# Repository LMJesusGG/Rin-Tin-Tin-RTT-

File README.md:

# Rin-Tin-Tin-RTT
Battlebot controlado a distancia, por medio de un microprocesador ESP 32 Wroom, tipo Drum Spinner inspirado en el Minotaur.

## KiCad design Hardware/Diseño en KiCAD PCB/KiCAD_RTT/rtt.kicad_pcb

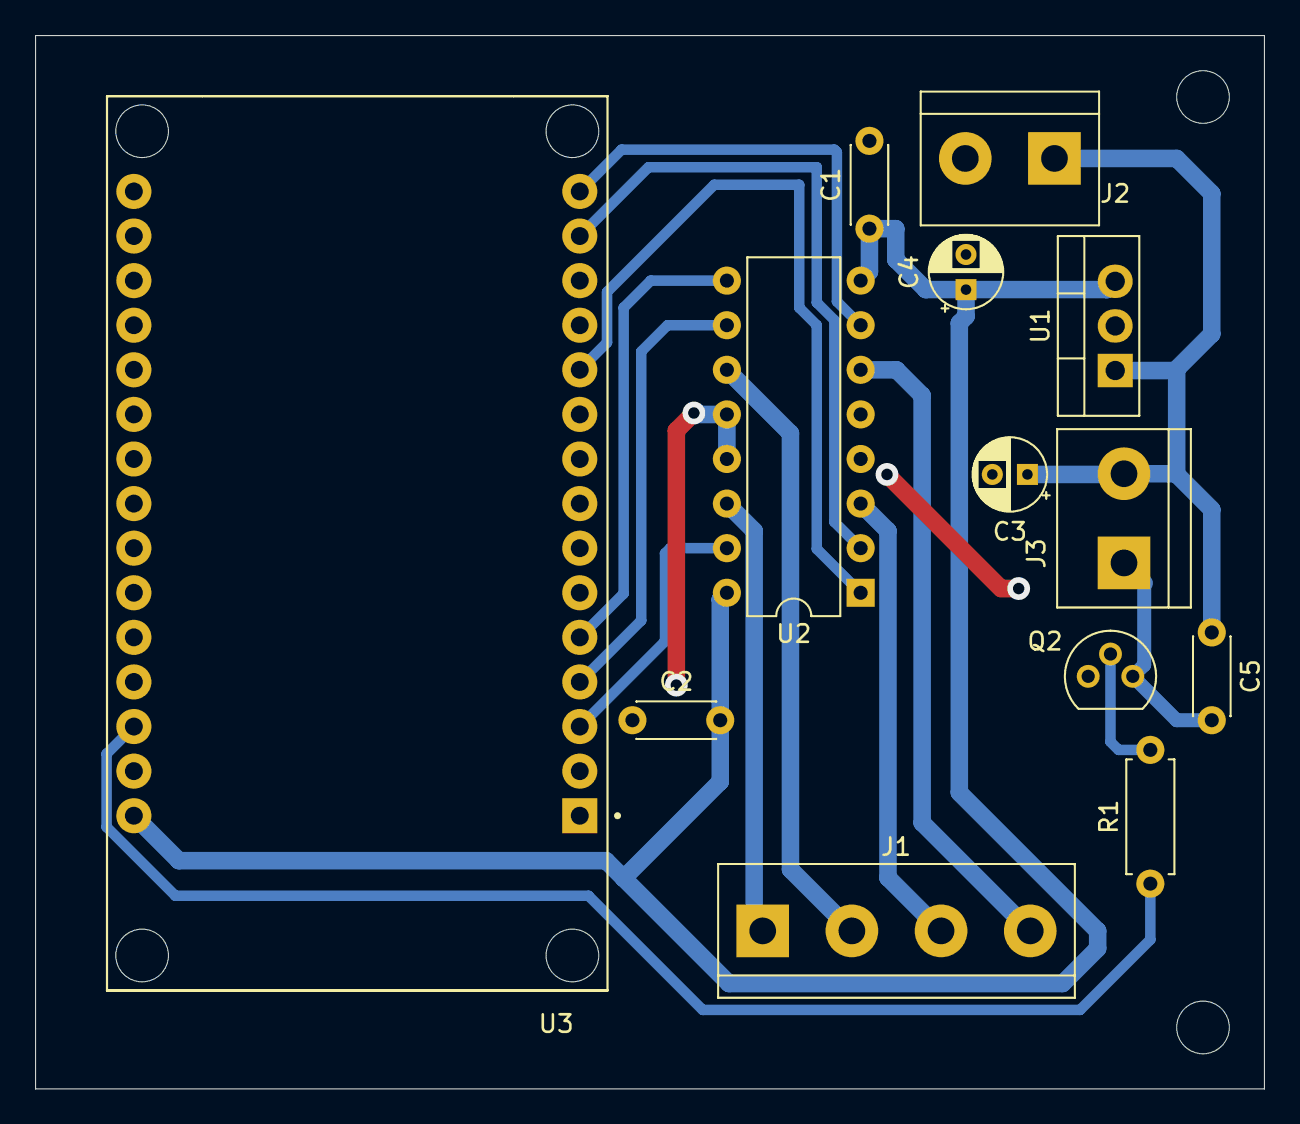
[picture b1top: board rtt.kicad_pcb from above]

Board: 2 copper layers, 70.0 x 60.0 mm, 13 parts (0 on the bottom side), 16 nets.

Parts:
C1, C2, C5: C; C_Disc_D4.3mm_W1.9mm_P5.00mm
C3, C4: C_Polarized; CP_Radial_D4.0mm_P2.00mm
J1: Screw_Terminal_01x04; TerminalBlock_bornier-4_P5.08mm
J2: bateria_9v; TerminalBlock_bornier-2_P5.08mm
J3: motor_fuerza; TerminalBlock_bornier-2_P5.08mm
Q2: 2n2222a; TO-92
R1: R; R_Axial_DIN0207_L6.3mm_D2.5mm_P7.62mm_Horizontal
U1: LM7805_TO220; TO-220-3_Vertical
U2: L293D; DIP-16_W7.62mm
U3: ESP32-DEVKIT-V1; MODULE_ESP32_DEVKIT_V1

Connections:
+5V: C1.1, C2.2, C4.1, U1.3 (VO), U2.8 (VCC2), U2.16 (VCC1), U3.30 (VIN)
+9V: C3.1, C5.1, J2.1, J3.2, U1.1 (VI)
/1A: U2.2 (1A), U3.14 (D22)
/2A: U2.7 (2A), U3.15 (D23)
/3A: U2.10 (3A), U3.4 (D2)
/4A: U2.15 (4A), U3.3 (D15)
/EN12: U2.1 (EN1,2), U3.11 (D21)
/EN34: U2.9 (EN3,4), U3.5 (D4)
/motor_fuerza: C5.2, J3.1, Q2.3 (C)
/pot_1y: J1.3, U2.3 (1Y)
/pot_2y: J1.4, U2.6 (2Y)
/pot_3y: J1.2, U2.11 (3Y)
/pot_4y: J1.1, U2.14 (4Y)
/pwm: R1.1, U3.28 (D13)
GND: C1.2, C2.1, C3.2, C4.2, J2.2, Q2.1 (E), U1.2 (GND), U2.4 (GND), U2.5 (GND), U2.12 (GND), U2.13 (GND), U3.2 (GND), U3.29 (GND)
unnamed: Q2.2 (B), R1.2

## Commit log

2024-09-03 Update LICENSE
2024-09-03 Update files
    Libs for KiCAD
2024-09-11 Actualización archivos PCB
2024-09-11 Actualización imágenes 3d
2024-09-11 Optimización de carpetas
2024-09-25 Actualización archivos
2024-09-25 Reorganización carpetas
2024-09-25 Actualización archiveros
2024-09-26 Archivos adicionales app
2024-09-26 Imagenes de apoyo
